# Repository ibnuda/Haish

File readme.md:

HAISH BAWEL

contoh desain pcb untuk [artikel](https://siskam.link/2019-11-27--bahasa--nggambar-kibor.html)
blog saya.

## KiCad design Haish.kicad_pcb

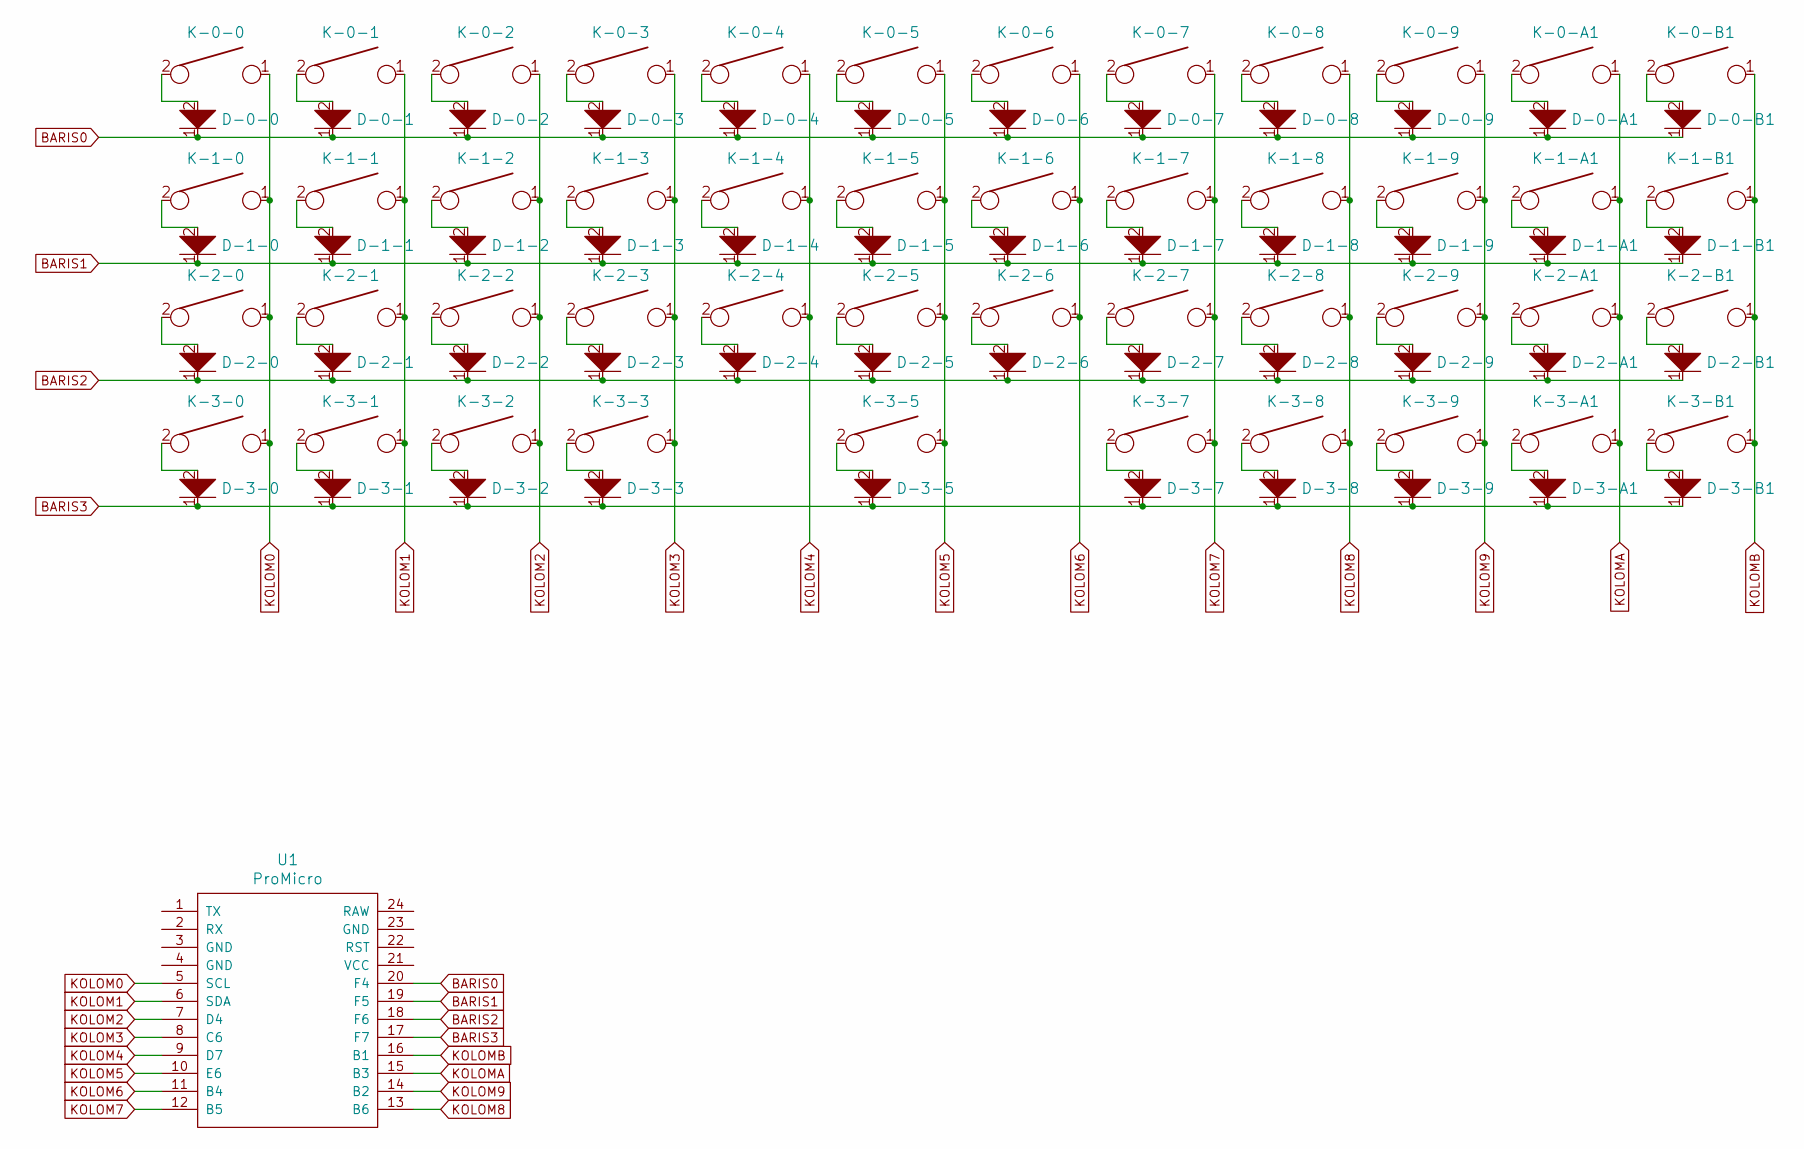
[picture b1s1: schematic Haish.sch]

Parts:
D-0-0, D-0-1, D-0-2, D-0-3, D-0-4, D-0-5, D-0-6, D-0-7, D-0-8, D-0-9, D-0-A1, D-0-B1, D-1-0, D-1-1, D-1-2, D-1-3, D-1-4, D-1-5, D-1-6, D-1-7, D-1-8, D-1-9, D-1-A1, D-1-B1, D-2-0, D-2-1, D-2-2, D-2-3, D-2-4, D-2-5, D-2-6, D-2-7, D-2-8, D-2-9, D-2-A1, D-2-B1, D-3-0, D-3-1, D-3-2, D-3-3, D-3-5, D-3-7, D-3-8, D-3-9, D-3-A1, D-3-B1: D; Diode
K-0-0, K-0-1, K-0-2, K-0-3, K-0-4, K-0-5, K-0-6, K-0-7, K-0-8, K-0-9, K-0-A1, K-1-1, K-1-2, K-1-3, K-1-4, K-1-5, K-1-6, K-1-7, K-1-8, K-1-9, K-1-A1, K-1-B1, K-2-1, K-2-2, K-2-3, K-2-4, K-2-5, K-2-6, K-2-7, K-2-8, K-2-9, K-2-A1, K-2-B1, K-3-1, K-3-5, K-3-9, K-3-A1, K-3-B1: KEYSW; MX_PCB_100H
K-0-B1, K-1-0, K-3-0, K-3-2, K-3-8: KEYSW; MX_PCB_125H
K-2-0: KEYSW; MX_PCB_175H
K-3-3: KEYSW; MX_PCB_225H
K-3-7: KEYSW; MX_PCB_275H
U1: ProMicro; ArduinoProMicro-ZigZag

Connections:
BARIS0: D-0-0.1, D-0-1.1, D-0-2.1, D-0-3.1, D-0-4.1, D-0-5.1, D-0-6.1, D-0-7.1, D-0-8.1, D-0-9.1, D-0-A1.1, D-0-B1.1, U1.20 (F4)
BARIS1: D-1-0.1, D-1-1.1, D-1-2.1, D-1-3.1, D-1-4.1, D-1-5.1, D-1-6.1, D-1-7.1, D-1-8.1, D-1-9.1, D-1-A1.1, D-1-B1.1, U1.19 (F5)
BARIS2: D-2-0.1, D-2-1.1, D-2-2.1, D-2-3.1, D-2-4.1, D-2-5.1, D-2-6.1, D-2-7.1, D-2-8.1, D-2-9.1, D-2-A1.1, D-2-B1.1, U1.18 (F6)
BARIS3: D-3-0.1, D-3-1.1, D-3-2.1, D-3-3.1, D-3-5.1, D-3-7.1, D-3-8.1, D-3-9.1, D-3-A1.1, D-3-B1.1, U1.17 (F7)
KOLOM0: K-0-0.1, K-1-0.1, K-2-0.1, K-3-0.1, U1.5 (SCL)
KOLOM1: K-0-1.1, K-1-1.1, K-2-1.1, K-3-1.1, U1.6 (SDA)
KOLOM2: K-0-2.1, K-1-2.1, K-2-2.1, K-3-2.1, U1.7 (D4)
KOLOM3: K-0-3.1, K-1-3.1, K-2-3.1, K-3-3.1, U1.8 (C6)
KOLOM4: K-0-4.1, K-1-4.1, K-2-4.1, U1.9 (D7)
KOLOM5: K-0-5.1, K-1-5.1, K-2-5.1, K-3-5.1, U1.10 (E6)
KOLOM6: K-0-6.1, K-1-6.1, K-2-6.1, U1.11 (B4)
KOLOM7: K-0-7.1, K-1-7.1, K-2-7.1, K-3-7.1, U1.12 (B5)
KOLOM8: K-0-8.1, K-1-8.1, K-2-8.1, K-3-8.1, U1.13 (B6)
KOLOM9: K-0-9.1, K-1-9.1, K-2-9.1, K-3-9.1, U1.14 (B2)
KOLOMA: K-0-A1.1, K-1-A1.1, K-2-A1.1, K-3-A1.1, U1.15 (B3)
KOLOMB: K-0-B1.1, K-1-B1.1, K-2-B1.1, K-3-B1.1, U1.16 (B1)
unnamed: D-0-0.2, K-0-0.2
unnamed: D-0-1.2, K-0-1.2
unnamed: D-0-2.2, K-0-2.2
unnamed: D-0-3.2, K-0-3.2
unnamed: D-0-4.2, K-0-4.2
unnamed: D-0-5.2, K-0-5.2
unnamed: D-0-6.2, K-0-6.2
unnamed: D-0-7.2, K-0-7.2
unnamed: D-0-8.2, K-0-8.2
unnamed: D-0-9.2, K-0-9.2
unnamed: D-0-A1.2, K-0-A1.2
unnamed: D-0-B1.2, K-0-B1.2
unnamed: D-1-0.2, K-1-0.2
unnamed: D-1-1.2, K-1-1.2
unnamed: D-1-2.2, K-1-2.2
unnamed: D-1-3.2, K-1-3.2
unnamed: D-1-4.2, K-1-4.2
unnamed: D-1-5.2, K-1-5.2
unnamed: D-1-6.2, K-1-6.2
unnamed: D-1-7.2, K-1-7.2
unnamed: D-1-8.2, K-1-8.2
unnamed: D-1-9.2, K-1-9.2
unnamed: D-1-A1.2, K-1-A1.2
unnamed: D-1-B1.2, K-1-B1.2
unnamed: D-2-0.2, K-2-0.2
unnamed: D-2-1.2, K-2-1.2
unnamed: D-2-2.2, K-2-2.2
unnamed: D-2-3.2, K-2-3.2
unnamed: D-2-4.2, K-2-4.2
unnamed: D-2-5.2, K-2-5.2
unnamed: D-2-6.2, K-2-6.2
unnamed: D-2-7.2, K-2-7.2
unnamed: D-2-8.2, K-2-8.2
unnamed: D-2-9.2, K-2-9.2
unnamed: D-2-A1.2, K-2-A1.2
unnamed: D-2-B1.2, K-2-B1.2
unnamed: D-3-0.2, K-3-0.2
unnamed: D-3-1.2, K-3-1.2
unnamed: D-3-2.2, K-3-2.2
unnamed: D-3-3.2, K-3-3.2
unnamed: D-3-5.2, K-3-5.2
unnamed: D-3-7.2, K-3-7.2
unnamed: D-3-8.2, K-3-8.2
unnamed: D-3-9.2, K-3-9.2
unnamed: D-3-A1.2, K-3-A1.2
unnamed: D-3-B1.2, K-3-B1.2

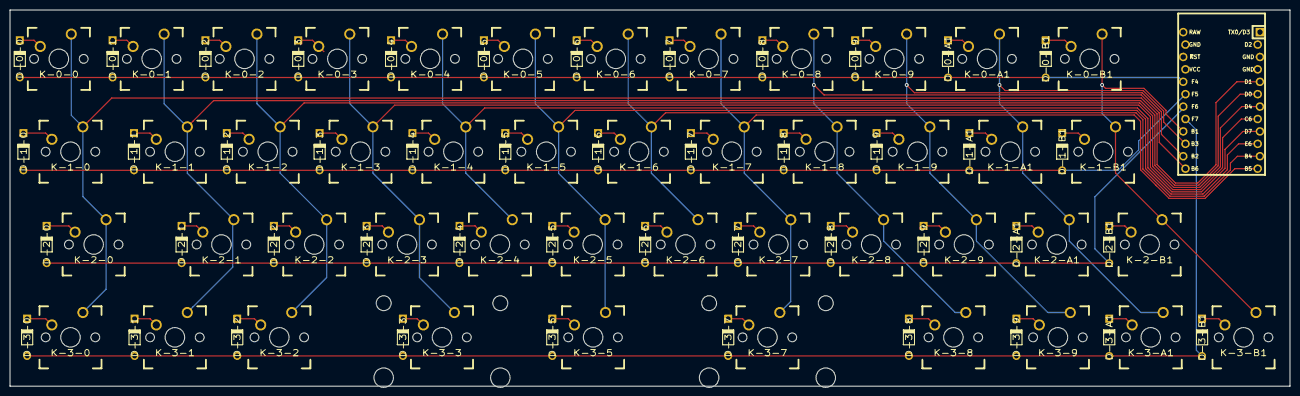
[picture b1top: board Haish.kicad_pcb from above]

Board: 2 copper layers, 262.0 x 77.0 mm, 93 parts (1 on the bottom side), 62 nets.

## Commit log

2019-11-29 init. commit.
2019-11-29 hhmm...' '
2019-11-29 lali readme.md.
2019-12-02 lanjut, bang.
2019-12-02 rampung.
